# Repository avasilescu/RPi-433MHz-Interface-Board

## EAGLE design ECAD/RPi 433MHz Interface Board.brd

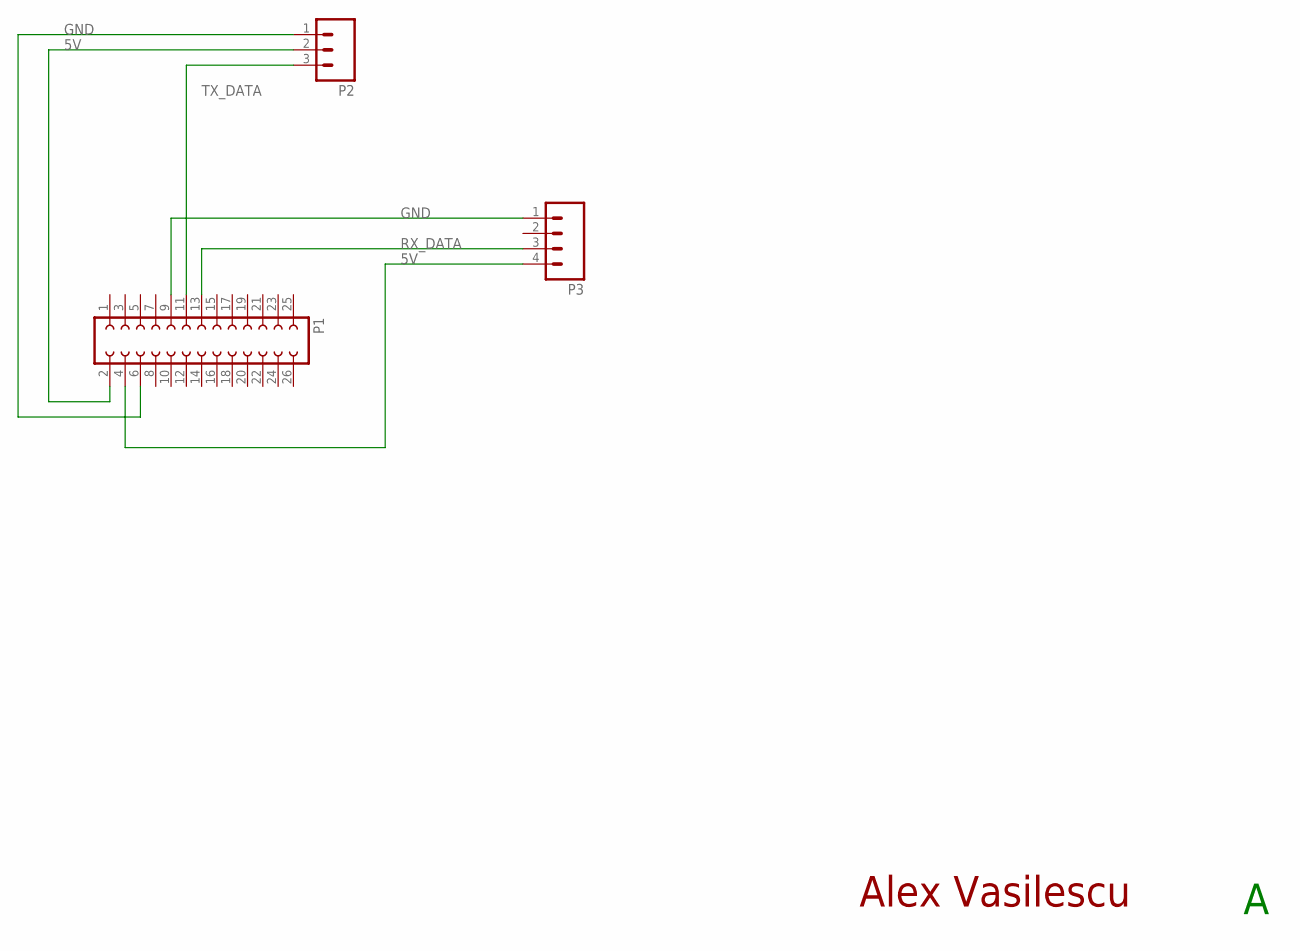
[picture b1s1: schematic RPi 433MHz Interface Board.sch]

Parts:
P1: FE13-2
P2: M03POLAR; MOLEX-1X3
P3: M04POLAR; MOLEX-1X4
U$1: AV-LOGO

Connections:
5V: P1.2, P1.4, P2.2, P3.4
GND: P1.6, P1.9, P2.1, P3.1
RX_DATA: P1.13, P3.3
TX_DATA: P1.11, P2.3

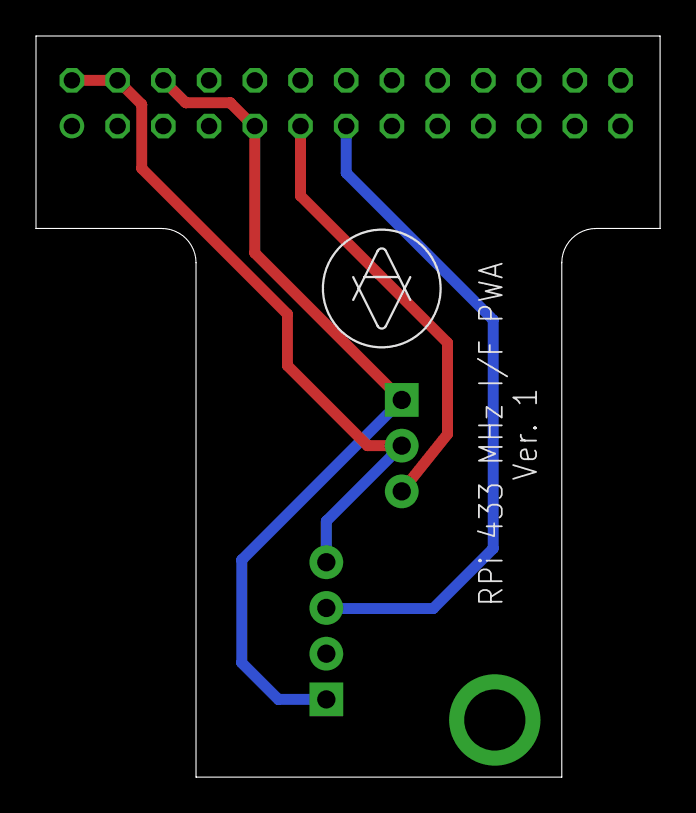
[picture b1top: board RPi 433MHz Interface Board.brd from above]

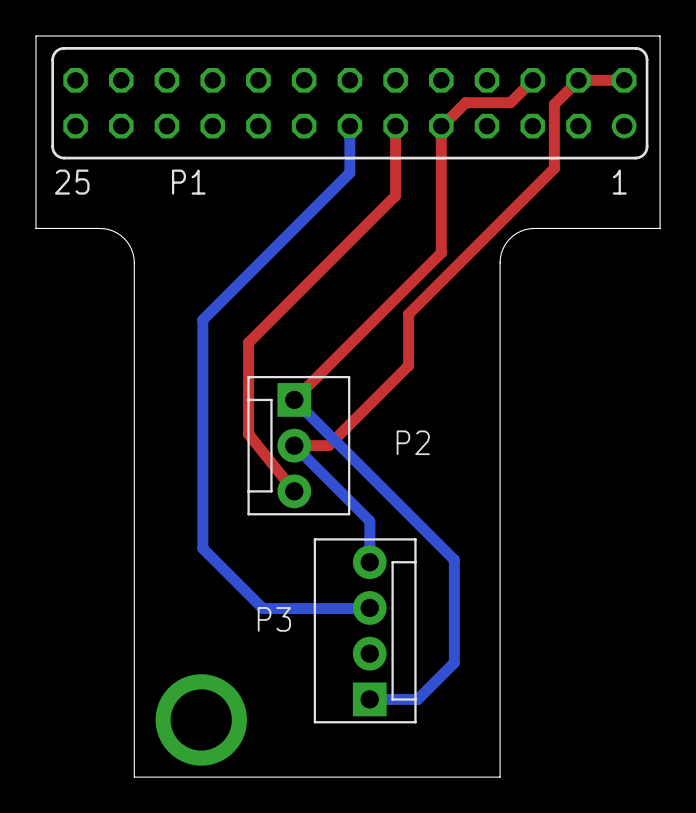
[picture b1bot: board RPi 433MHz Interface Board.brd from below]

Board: 2 copper layers, 34.7 x 41.2 mm, 4 parts (3 on the bottom side), 4 nets.

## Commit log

2016-05-06 Add EAGLE schematic, layout, and gerber files.
2016-05-06 Add SolidWorks files of transmiter and receiver boards, headers, jumper pins, breakout board, RaspberryPi, and SD Card.
2016-05-06 Add DRILEGEND.CFG file, Zip file of gerbers, and Eagle Project File.

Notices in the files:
parts and their libraries:
SparkFun-Connectors: Licensing: Creative Commons ShareAlike 4.0 International - https://creativecommons.org/licenses/by-sa/4.0
